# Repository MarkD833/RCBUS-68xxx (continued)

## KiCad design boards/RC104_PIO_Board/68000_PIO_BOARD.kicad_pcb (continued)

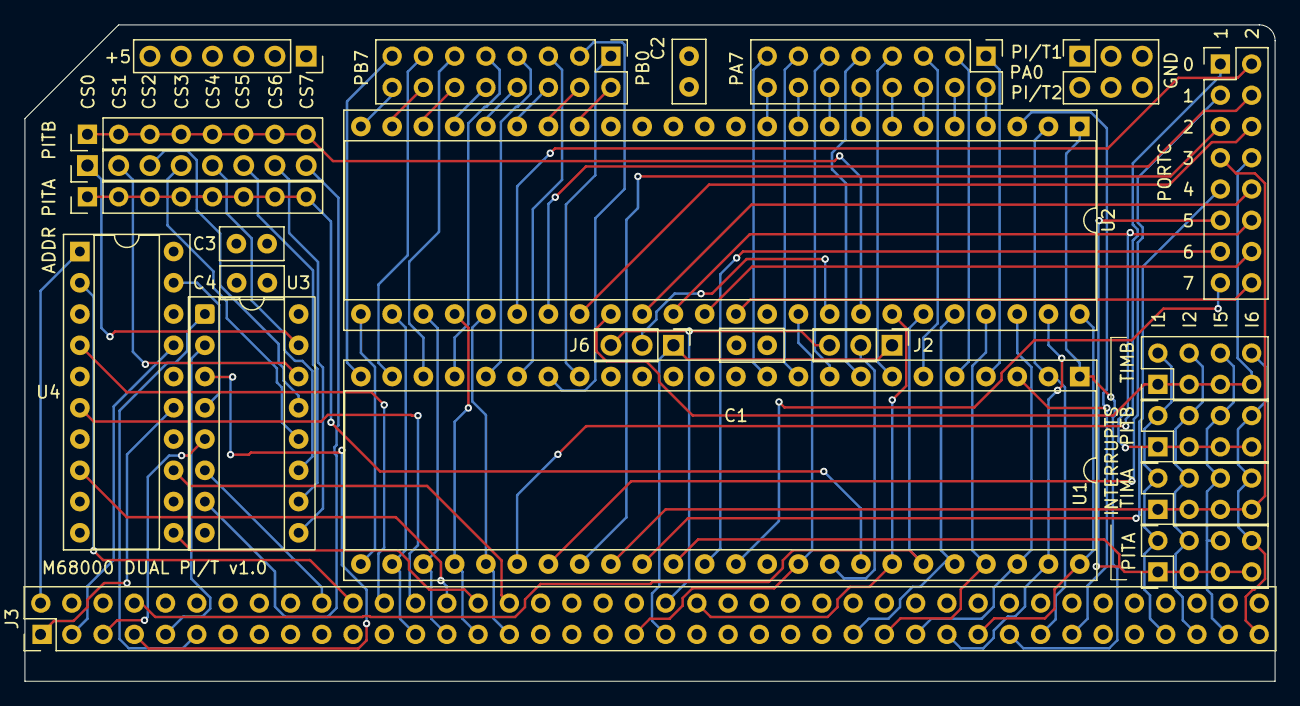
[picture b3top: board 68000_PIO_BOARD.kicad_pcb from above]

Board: 4 copper layers, 101.6 x 53.3 mm, 23 parts (0 on the bottom side), 99 nets.

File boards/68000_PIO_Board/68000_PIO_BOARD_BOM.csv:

"Reference","Value","Datasheet","Footprint","Qty","Description"
"C1,C2,C3,C4","100n","~","Capacitor_THT:C_Disc_D5.0mm_W2.5mm_P2.50mm","4","Unpolarized ceramic capacitor"
"J1,J4,J5","Conn_02x08_Odd_Even","~","MyLibrary2023:PinHeader_2x08_P2.54mm_Vertical","3","Generic connector, double row, 02x08, right angle"
"J2,J6","Conn_01x03","~","Connector_PinHeader_2.54mm:PinHeader_1x03_P2.54mm_Vertical","2","Generic connector, single row, 01x03"
"J3","RCBus_80PIN_68000","~","MyLibrary2023:RCBus_80p_Medium","1","Generic connector, double row, 02x40, right angle"
"J7,J12,J13","Conn_01x08","~","Connector_PinHeader_2.54mm:PinHeader_1x08_P2.54mm_Vertical,MyLibrary2023:PinHeader_1x08_P2.54mm_Vertical","3","Generic connector, single row, 01x08"
"J8,J9,J10,J11","Conn_02x04_Odd_Even","~","MyLibrary2023:PinHeader_2x04_P2.54mm_Vertical","4","Generic connector, double row, 02x04"
"J14","Conn_02x03_Odd_Even","~","Connector_PinSocket_2.54mm:PinSocket_2x03_P2.54mm_Vertical","1","Generic connector, double row, 02x03, right angle"
"J15","Conn_01x06","~","Connector_PinSocket_2.54mm:PinSocket_1x06_P2.54mm_Vertical","1","Generic connector, single row, 01x06, right angle"
"U1,U2","68230","","MyLibrary2023:DIP-48_W15.24mm_Socket","2","Parallel Interface / Timer"
"U3","74LS138","http://www.ti.com/lit/gpn/sn74LS138","Package_DIP:DIP-16_W7.62mm_Socket","1","Decoder 3 to 8 active low outputs"
"U4","74LS688","http://www.ti.com/lit/gpn/sn74LS688","MyLibrary2023:DIP-20_W7.62mm_Socket","1","8-bit magnitude comparator"

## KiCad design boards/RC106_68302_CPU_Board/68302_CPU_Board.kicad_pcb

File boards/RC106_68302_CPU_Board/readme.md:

# 68302 Processor Board

# Details
The processor board consists of a PGA packaged MC68302 processor, bits of glue logic and the processor clock source.

The processor board is designed to plug into an RCBus-80 backplane and expects to find the stack pointer and initial program counter addresses at location 0x000000 onwards.

If using latest version of the MON302 that supports ROM & RAM remapping via software then the RC102 ROM/RAM board should not be used without some hardware modification.

## Reset
The reset signal for the processor board must be supplied externally, entering the board via pin 20 of the RCBus connector. This should not be an issue if you are using one of Steve Cousins's backplanes.

## Processor Clock
The processor/system clock source is an oscillator in an 8-pin DIL/DIP can (X1 in the schematic). I used a turned pin socket to hold the oscillator as it made it easy to quickly swap in and out oscillators of different frequencies. Basic testing was done with a 7.3728MHz oscillator.

A **note of caution** when using a socketed oscillator - there is the possibility that the metal can of the oscillator could accidentally short out pins on the next board. Please be aware of this.

The 68302 doesn't have an E clock signal like the 68000 does so I chose to have the option to route the output of Timer #1 to the RCBus CLOCK2 pin (61) via a jumper.

Note that the CLOCK2 pin may also be used by the serial, parallel and multifunction boards (via jumpers on their boards) to share a clock source between them - usually to feed the baud rate generators and timers. If this feature is used, then the CLOCK2 jumper must not be fitted.

## Chip Selects
The 68302 processor has 4 user programmable chip select signals - /CS0, /CS1, /CS2 & /CS3.

/CS0 is automatically configured by the processor at reset for an 8K block of memory starting at address $000000. /CS0 would normally be used to select a non-volatile memory device that holds the boot code. However there's a solder jumper (JP1) that can be used to route /CS0 to RCBus pin 45 if required.
+ RC102 ROM/RAM board includes address decoding to select the pair of ROMs at address $000000 so /CS0 isn't needed (must use older version of MON302)
+ RC107 ROM/RAM board supports external chip selects - see RC107 readme for more details
+ RC208 ROM/RAM board **MUST** set the ROM chip select to EXT

/CS1 is disabled by the processor at reset. I intended this chip select to select the volatile memory device on my RC107 ROM/RAM board. There's a solder jumper (JP2) that can be used to route /CS1 to RCBus pin 46 if required.
+ RC102 ROM/RAM board includes address decoding to select the pair of RAMs at address $100000 so /CS1 isn't needed (must use older version of MON302)
+ RC107 ROM/RAM board supports external chip selects - see RC107 readme for more details
+ RC208 ROM/RAM board **MUST** set the RAM chip select to EXT

/CS2 is disabled by the processor at reset. This chip select signal is used to enable access to the RCBus memory and i/o spaces. The /CS2 address decoding is configured for a 128K block of memory that is split into two 64K blocks by half of a 74LS139. Accessing the lower 64K block generates an /MREQ on the RCBus and accessing the upper 64K block generates an /IORQ on the RCBus.

**NOTE:** If using the newer version of MON302 that supports remapping of the ROM and RAM address spaces, then please see the relevant ROM/RAM board readme file for details on the hardware modifications needed to the ROM/RAM board to support this.

## DTACK & Bus Error
The user programmable chip select signals can also be configured to internally generate the DTACK signal so no external gates are required. My ROM/RAM board generates its own DTACK signal so DTACK is disabled for /CS0 & /CS1. /CS2 is configured to for 2 wait states.

The 68302 processor also includes an internal hardware watchdog that is enabled at reset and will generate a Bus Error if a DTACK isn't generated by the internal chip select logic or an external device.

## Serial Ports
Two of the 68302 serial ports - SCC1 & SCC2 - are fed to 6-pin connectors at the board edge. The layout of the 6 pins is compatible with an FTDI USB-TTL Serial interface board.

## SPI Port
The 68302 hardware SPI port (via SCC3 pins) is available on J6. Also on J6 is a chip select for the SPI device which is connected to port pin PB8 of the 68302.
 
## RCBus Signals
The RCBus specification (v1.0) doesn't specifically mention the 68000 in the backplane signal assignments table so there's a bit of wiggle room on the pins used.

I've stuck to the same signals for pins 1-40. The M1 signal isn't used and should have a 4K7 pullup resistor (manually added as I forgot it in my release 2.0 board!) and the USER1..USER4 which are used for the level 1, 3, 5 & 6 autovector interrupts.

Pins 41-80 carry D8..D15 as well as the higher address bits. Pins 41..44 have been used to carry some 68000 specific signals.

The current signal list is in the RCBus 68000 Pinout PDF file.

For the 68302 board, I have introduced 2 additional signals that can be routed onto the backplane to expose the /CS0 (pin 45) and /CS1 (pin 46) chip select signals. These are disconnected by default but can easily be connected by shorting solder jumpers JP1 (/CS0) and JP2 (/CS1) on the rear of the board.

The output of Timer #1 can be routed to the CLOCK2 pin to provide a clock source for other boards if required.

## RCBus memory space
The RCBus memory space is available via a 128K window in the 68302 address space. The hardware uses /CS2 to select this memory space with A16 determining either memory or I/O space as follows:
| Address Range | Signal |
| :---- | :---- |
| 0xFC0000..0xFCFFFF | /MREQ goes low |
| 0xFD0000..0xFDFFFF | /IORQ goes low |

This partial decoding results in the RCBus I/O memory space appearing multiple times within the 68000 address range. A DTACK signal is generated internally for any access to the RCBus whether there is a device present at that address or not.

For both I/O and memory spaces, consecutive memory locations are accessed on the ODD bytes such that I/O address 0x00 is accessed at address 0xFD0001, address 0x01 is accessed at address 0xFD0003 etc.

## Onboard LEDs
There are 4 LEDs on the board indicate accesses to the RCBus I/O and memory spaces as well as a HALT LED and a user LED (connected to port pin PB9).

## Power
The complete RCBus system can be powered from the 5V pin of one of the USB-TTL serial connectors by fitting a jumper in place on the appropriate pins of J3.

Note that there is a current limit of 500mA - imposed by the host system USB hardware - when the system is powered this way. It is relatively easy to exceed this limit once several boards are in use and I recommend that the system be powered from an external 5V supply connected to the RCBus backplane instead.

# Board Assembly
Assembly of the board should be fairly straightforward as there are no surface mount devices to deal with, but see the note below regarding the 68302 socket.

If you choose have a turned pin socket for the system clock, then an 8-pin DIL turned pin socket can be used. I flipped the socket over - pins pointing upwards - and easily pushed out pins 2,3,6 & 7.

A **note of caution** when using a socketed oscillator - there is the possibility that the metal can of the oscillator could accidentally short out pins on the next board. Please be aware of this.

When fitting the 80-pin right angle connector, initially only solder a couple of pins at opposite ends of the connector so that you can make any adjustments if the board is not vertical when fitted to the backplane.

# Note on the MC68302 socket
I could not get hold of the official PGA socket for the 68302 so I had to make my own from some SIL turned pin socket strips. From an earlier experiment I learnt that the plastic housing is slightly too wide so you can't simply butt together 13 SIL strips to make a socket. Instead I had to alternate between rows of pins in the plastic housing and rows of individual pins like this:

This makes it a bit of a pain trying to get all the individual pins to play ball and line up with the PCB holes but it does work.

**Note:** Be careful with this method as I later discovered that the SIL turned pin sockets were not the low insertion force type. Once soldered into the board, the combined resistance of 132 turned pin sockets is such that the processor can't be removed without breaking it. The only way to get the processor out safely is by destroying the board with a handy rotary tool by cutting out the piece of board holding the processor and then carefully cutting off the pins very close to the board. The processor should then come away and the remains of the turned pin sockets can be easily removed individually. 

# Software
I've written a very simple monitor program for the 68302 board whick can be found in the ASM_CODE folder - called MON302. The monitor was initially developed using EASy68K.

## Interrupts
As the ROM is currently fixed at address 0x000000, the exception vector table addresses are also fixed. Exception vectors up to and including TRAP #15 each call their own handler stub within the monitor ROM. The remaining exception vectors are all directed to a single handler as they are not used within my design - i.e. vectored interrupts are not supported, only autovectored interrupts.

Each exception handler stub in the ROM (apart from bus error, address error and TRAP #15) looks up the start address of the actual exception handler code in a table of addresses held in RAM (which is initialised by the montor program). The table is located at the start of RAM occupying addresses 0x100000..0x1003FF and is laid out just like a normal exception vector table.

In order to use your own exception handler, you simply over write the RAM exception vector table entry with the address of your own handler.

# Jumpers
+ J1: Fit jumper to route Timer #1 output onto RCBus CLOCK2 but only if CLOCK2 is **not** being used to share a clock between the SIO, PIO and MFP boards.
+ J3: External 5V supply for the system
  + 1-2 : Power the system from the USB-TTL Serial board on Serial #1
  + 2-3 : Power the system from the USB-TTL Serial board on Serial #2
+ J4: Serial #1 port from SCC1
+ J5: Serial #2 port from SCC2
+ J6: SPI port

# Solder Jumpers
The 2 solder jumpers are located on the rear of the board and are used to route the 68302 /CS0 and /CS1 chip select signals onto the RCBus. With these jumpers soldered and a simple modification to the ROM/RAM board, the 68302 can boot from ROM at address $0000 and then swap the ROM and RAM so that RAM is located at address $0000.

+ JP1: solder this jumper to connect /CS0 to RCBus pin 45.
+ JP2: solder this jumper to connect /CS1 to RCBus pin 46.

# Errors
A fundamental flaw in the way interrupts are handled has come to light. This appears to only affect interrupts generated internally by the 68302 such as serial port or timer interrupts. It seems that when the 68302 generates its own interrupt - when an SCC receive buffer is full for example - it exposes this interrupt to the outside world by setting its FC0, FC1 & FC2 bits to a 7. This causes the current external logic to drive the /AVEC pin and create a level 4 autovectored interrupt rather than a level 4 vectored interrupt. All 68302 internally generated interrupts are level 4. The end result is that all internally generated interrupts get funneled through the single AV4 exception handler.

# Thoughts / Enhancements
+ Should I have used SCC1 for the monitor port?
  + CTS1 is in input to SCC1 that can be used to tell SCC1 to stop transmitting.
  + RTS1 is an output from SCC1 and is asserted when SCC1 Tx buffer has data to send.
  + Don't appear to have software control over these pins to be able to tell the host PC to stop transmitting data to SCC1.
+ SCC2 provides software control of RTS2 (Port pin PA5) and CTS2 (Port pin PA4). Therefore can tell host PC to stop transmitting via software if our Rx buffers fill up.
+ SCC3 has no handshaking as the pins are used for the SPI interface.
+ For 115200 baud with RTS/CTS handshaking for quick xfer of srec files then it looks like SCC2 would be the better choice.

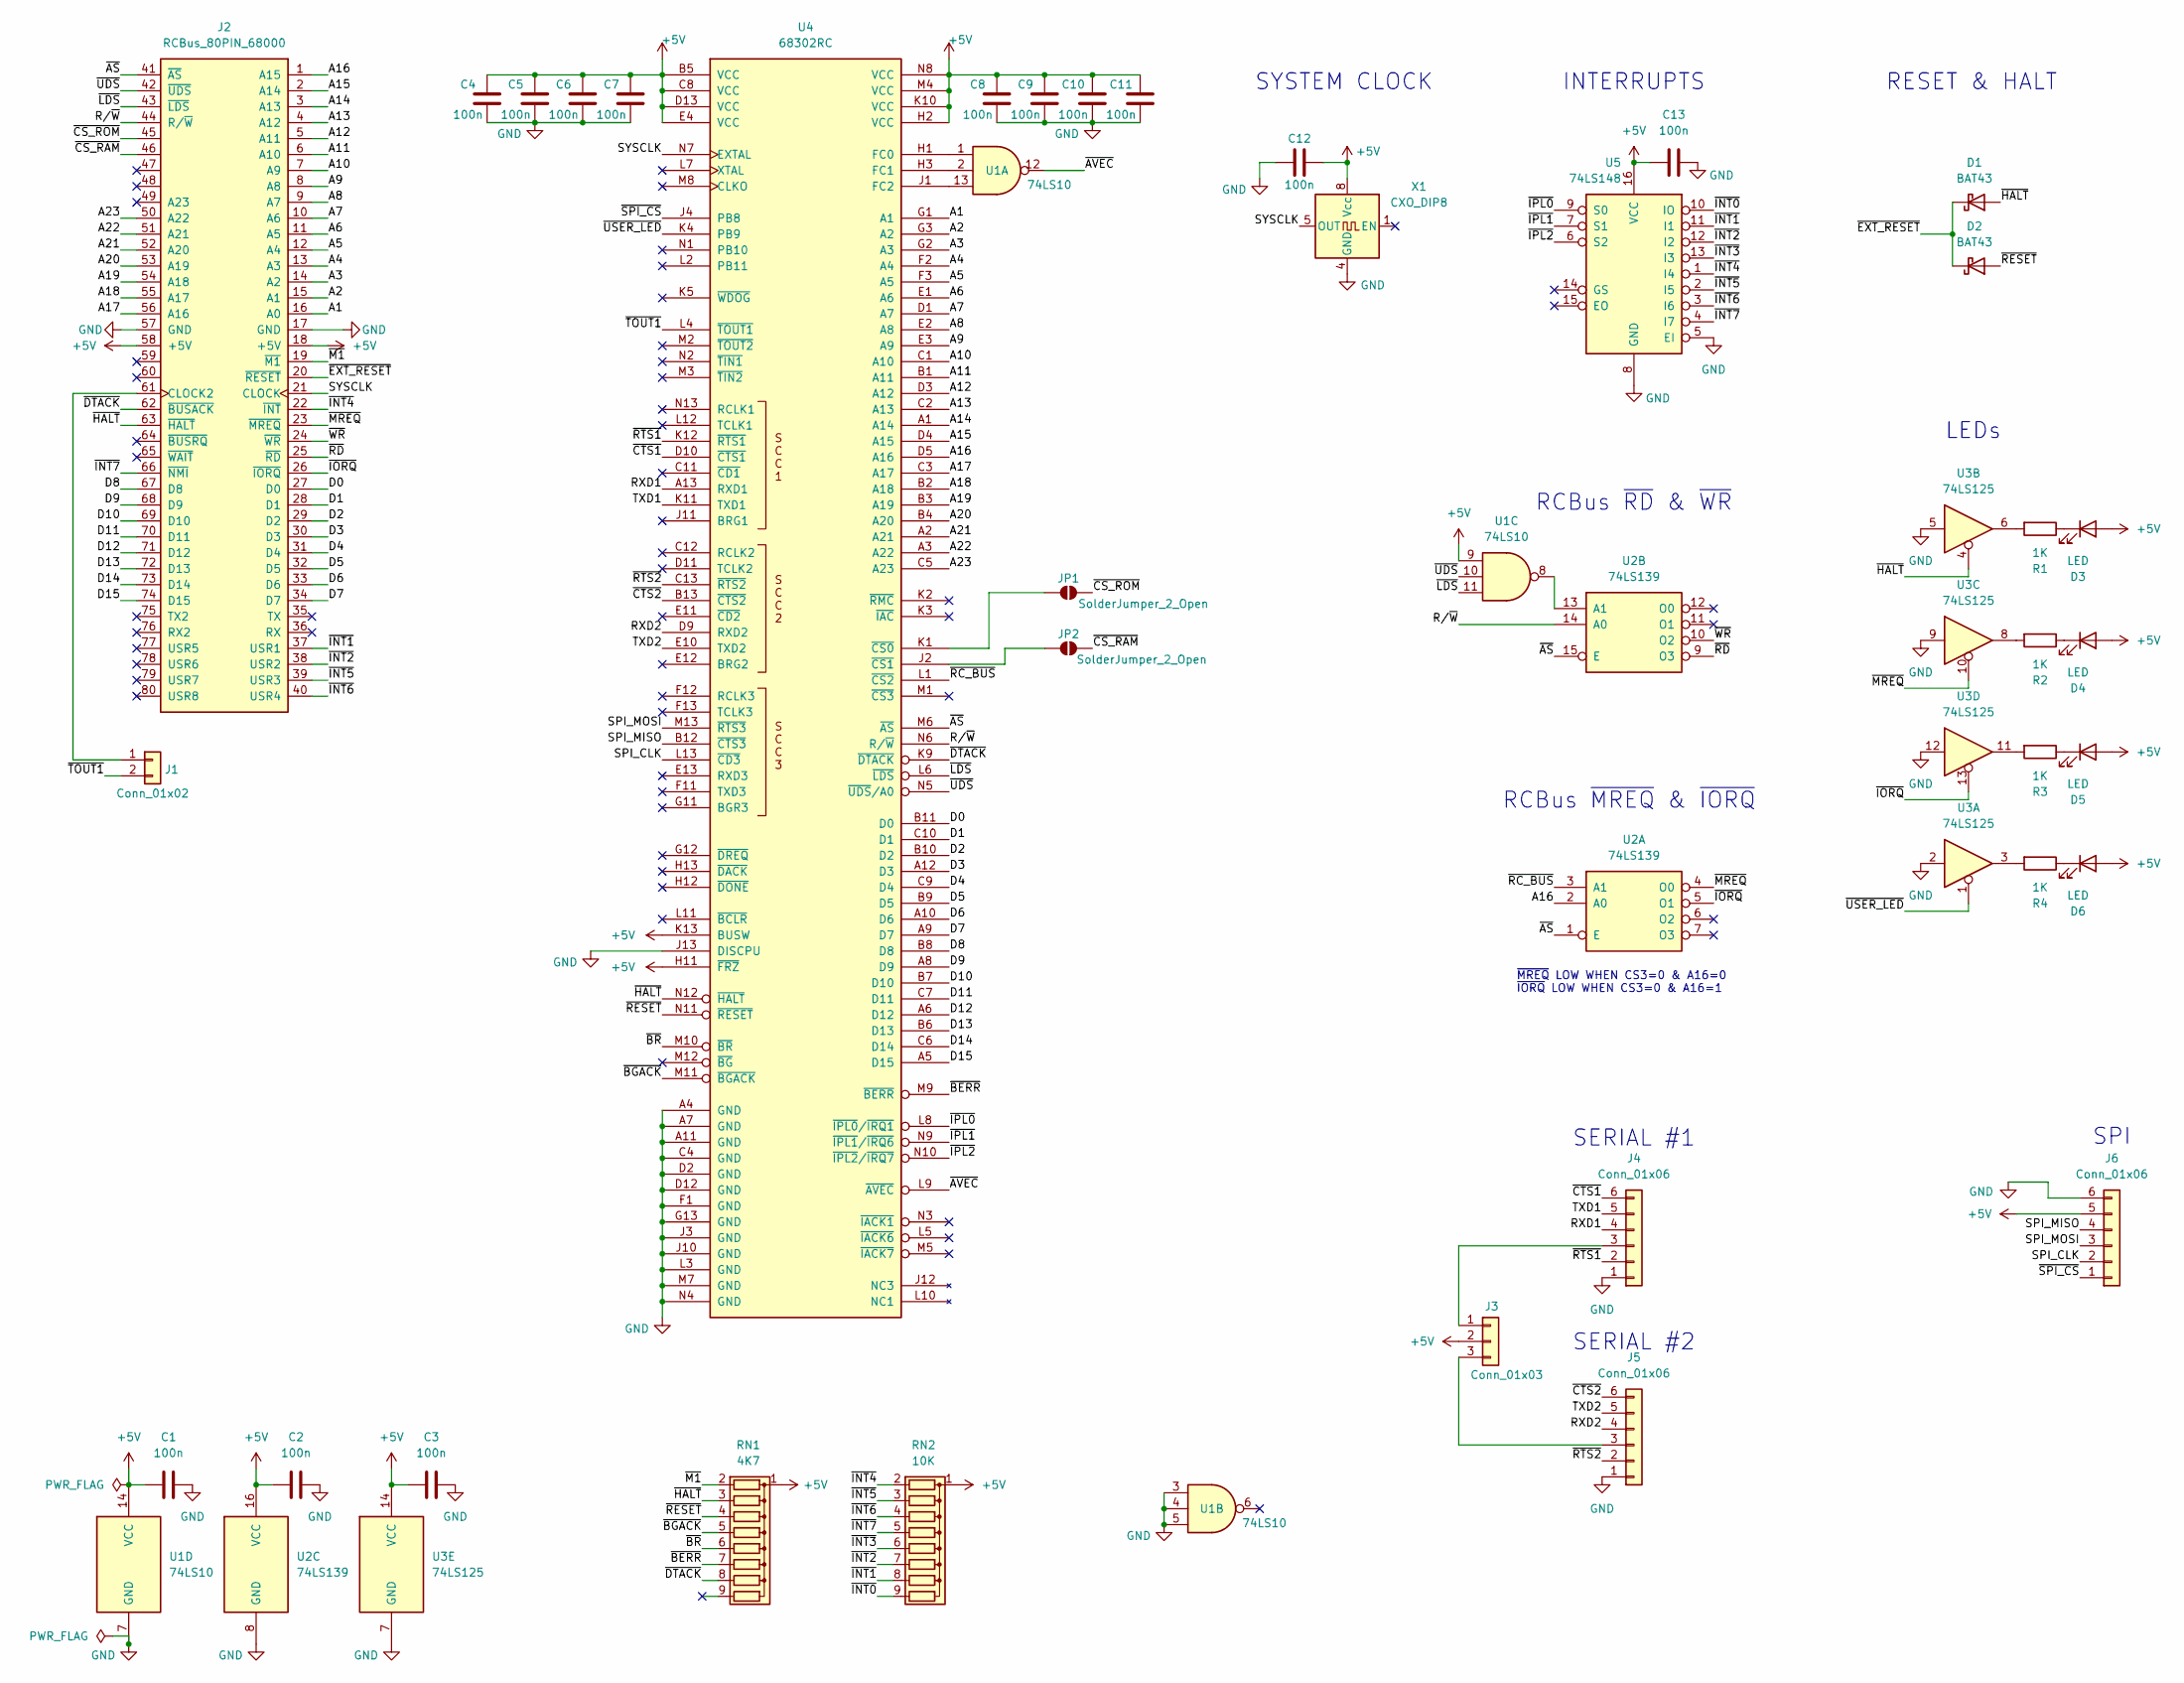
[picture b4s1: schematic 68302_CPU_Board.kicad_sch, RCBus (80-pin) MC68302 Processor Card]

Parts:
C1, C2, C3, C4, C5, C6, C7, C8, C9, C10, C11, C12, C13: 100n; C_Disc_D5.0mm_W2.5mm_P2.50mm
D1, D2: BAT43; D_DO-35_SOD27_P7.62mm_Horizontal
D3, D4, D5, D6: LED; LED_D3.0mm
J1: Conn_01x02; PinHeader_1x02_P2.54mm_Vertical
J2: RCBus_80PIN_68000; RCBus_80p_Medium
J3: Conn_01x03; PinHeader_1x03_P2.54mm_Vertical
J4, J5, J6: Conn_01x06; PinSocket_1x06_P2.54mm_Horizontal
JP1, JP2: SolderJumper_2_Open; SolderJumper-2_P1.3mm_Open_Pad1.0x1.5mm
R1, R2, R3, R4: 1K; R_Axial_DIN0207_L6.3mm_D2.5mm_P7.62mm_Horizontal
RN1: 4K7; R_Array_SIP9
RN2: 10K; R_Array_SIP9
U1: 74LS10; DIP-14_W7.62mm_Socket
U2: 74LS139; DIP-16_W7.62mm_Socket
U3: 74LS125; DIP-14_W7.62mm_Socket
U4: 68302RC; PGA132
U5: 74LS148; DIP-16_W7.62mm_Socket
X1: CXO_DIP8; Oscillator_DIP-8

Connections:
+5V: C1.1, C2.1, C3.1, C4.2, C5.2, C6.2, C7.2, C8.2, C9.2, C10.2, C11.2, C12.2, C13.1, D3.2 (A), D4.2 (A), D5.2 (A), D6.2 (A), J2.18 (+5V), J2.58 (+5V), J3.2, J6.5, RN1.1 (common), RN2.1 (common), U1.9, U1.14 (VCC), U2.16 (VCC), U3.14 (VCC), U4.B5 (VCC), U4.C8 (VCC), U4.D13 (VCC), U4.E4 (VCC), U4.H2 (VCC), U4.H11 (~FRZ), U4.K10 (VCC), U4.K13 (BUSW), U4.M4 (VCC), U4.N8 (VCC), U5.16 (VCC), X1.8 (Vcc)
/A1: J2.16 (A0), U4.G1 (A1)
/A2: J2.15 (A1), U4.G3 (A2)
/A3: J2.14 (A2), U4.G2 (A3)
/A4: J2.13 (A3), U4.F2 (A4)
/A5: J2.12 (A4), U4.F3 (A5)
/A6: J2.11 (A5), U4.E1 (A6)
/A7: J2.10 (A6), U4.D1 (A7)
/A8: J2.9 (A7), U4.E2 (A8)
/A9: J2.8 (A8), U4.E3 (A9)
/A10: J2.7 (A9), U4.C1 (A10)
/A11: J2.6 (A10), U4.B1 (A11)
/A12: J2.5 (A11), U4.D3 (A12)
/A13: J2.4 (A12), U4.C2 (A13)
/A14: J2.3 (A13), U4.A1 (A14)
/A15: J2.2 (A14), U4.D4 (A15)
/A16: J2.1 (A15), U2.2 (A0), U4.D5 (A16)
/A17: J2.56 (A16), U4.C3 (A17)
/A18: J2.55 (A17), U4.B2 (A18)
/A19: J2.54 (A18), U4.B3 (A19)
/A20: J2.53 (A19), U4.B4 (A20)
/A21: J2.52 (A20), U4.A2 (A21)
/A22: J2.51 (A21), U4.A3 (A22)
/A23: J2.50 (A22), U4.C5 (A23)
/D0: J2.27 (D0), U4.B11 (D0)
/D1: J2.28 (D1), U4.C10 (D1)
/D2: J2.29 (D2), U4.B10 (D2)
/D3: J2.30 (D3), U4.A12 (D3)
/D4: J2.31 (D4), U4.C9 (D4)
/D5: J2.32 (D5), U4.B9 (D5)
/D6: J2.33 (D6), U4.A10 (D6)
/D7: J2.34 (D7), U4.A9 (D7)
/D8: J2.67 (D8), U4.B8 (D8)
/D9: J2.68 (D9), U4.A8 (D9)
/D10: J2.69 (D10), U4.B7 (D10)
/D11: J2.70 (D11), U4.C7 (D11)
/D12: J2.71 (D12), U4.A6 (D12)
/D13: J2.72 (D13), U4.B6 (D13)
/D14: J2.73 (D14), U4.C6 (D14)
/D15: J2.74 (D15), U4.A5 (D15)
/RXD1: J4.4, U4.A13 (RXD1)
/RXD2: J5.4, U4.D9 (RXD2)
/R/~W: J2.44 (R/~W), U2.14 (A0), U4.N6 (R/~W)
/SPI_CLK: J6.2, U4.L13 (~CD3)
/SPI_MISO: J6.4, U4.B12 (~CTS3)
/SPI_MOSI: J6.3, U4.M13 (~RTS3)
/SYSCLK: J2.21 (CLOCK), U4.N7 (EXTAL), X1.5 (OUT)
/TXD1: J4.5, U4.K11 (TXD1)
/TXD2: J5.5, U4.E10 (TXD2)
/~AS: J2.41 (~AS), U2.1 (E), U2.15 (E), U4.M6 (~AS)
/~AVEC: U1.12, U4.L9 (~AVEC)
/~BERR: RN1.7 (R6), U4.M9 (~BERR)
/~BGACK: RN1.5 (R4), U4.M11 (~BGACK)
/~BR: RN1.6 (R5), U4.M10 (~BR)
/~CS_RAM: J2.46, JP2.2 (B)
/~CS_ROM: J2.45, JP1.2 (B)
/~CTS1: J4.6, U4.D10 (~CTS1)
/~CTS2: J5.6, U4.B13 (~CTS2)
/~DTACK: J2.62 (~BUSACK), RN1.8 (R7), U4.K9 (~DTACK)
/~EXT_RESET: D1.1 (K), D2.1 (K), J2.20 (~RESET)
/~HALT: D1.2 (A), J2.63 (~HALT), RN1.3 (R2), U3.4, U4.N12 (~HALT)
/~INT0: RN2.9 (R8), U5.10 (IO)
/~INT1: J2.37 (USR1), RN2.8 (R7), U5.11 (I1)
/~INT2: J2.38 (USR2), RN2.7 (R6), U5.12 (I2)
/~INT3: RN2.6 (R5), U5.13 (I3)
/~INT4: J2.22 (~INT), RN2.2 (R1), U5.1 (I4)
/~INT5: J2.39 (USR3), RN2.3 (R2), U5.2 (I5)
/~INT6: J2.40 (USR4), RN2.4 (R3), U5.3 (I6)
/~INT7: J2.66 (~NMI), RN2.5 (R4), U5.4 (I7)
/~IORQ: J2.26 (~IORQ), U2.5 (O1), U3.13
/~IPL0: U4.L8 (~IPL0/~IRQ1), U5.9 (S0)
/~IPL1: U4.N9 (~IPL1/~IRQ6), U5.7 (S1)
/~IPL2: U4.N10 (~IPL2/~IRQ7), U5.6 (S2)
/~LDS: J2.43 (~LDS), U1.11, U4.L6 (~LDS)
/~M1: J2.19 (~M1), RN1.2 (R1)
/~MREQ: J2.23 (~MREQ), U2.4 (O0), U3.10
/~RC_BUS: U2.3 (A1), U4.L1 (~CS2)
/~RD: J2.25 (~RD), U2.9 (O3)
/~RESET: D2.2 (A), RN1.4 (R3), U4.N11 (~RESET)
/~RTS1: J4.2, U4.K12 (~RTS1)
/~RTS2: J5.2, U4.C13 (~RTS2)
/~SPI_CS: J6.1, U4.J4 (PB8)
/~TOUT1: J1.2, U4.L4 (~TOUT1)
/~UDS: J2.42 (~UDS), U1.10, U4.N5 (~UDS/A0)
/~USER_LED: U3.1, U4.K4 (PB9)
/~WR: J2.24 (~WR), U2.10 (O2)
GND: C1.2, C2.2, C3.2, C4.1, C5.1, C6.1, C7.1, C8.1, C9.1, C10.1, C11.1, C12.1, C13.2, J2.17 (GND), J2.57 (GND), J4.1, J5.1, J6.6, U1.3, U1.4, U1.5, U1.7 (GND), U2.8 (GND), U3.2, U3.5, U3.7 (GND), U3.9, U3.12, U4.A4 (GND), U4.A7 (GND), U4.A11 (GND), U4.C4 (GND), U4.D2 (GND), U4.D12 (GND), U4.F1 (GND), U4.G13 (GND), U4.J3 (GND), U4.J10 (GND), U4.J13 (DISCPU), U4.L3 (GND), U4.M7 (GND), U4.N4 (GND), U5.5 (EI), U5.8 (GND), X1.4 (GND)
unnamed: D3.1 (K), R1.1
unnamed: D4.1 (K), R2.1
unnamed: D5.1 (K), R3.1
unnamed: D6.1 (K), R4.1
unnamed: J1.1, J2.61 (CLOCK2)
unnamed: J3.1, J4.3
unnamed: J3.3, J5.3
unnamed: JP1.1 (A), U4.K1 (~CS0)
unnamed: JP2.1 (A), U4.J2 (~CS1)
unnamed: R1.2, U3.6
unnamed: R2.2, U3.8
unnamed: R3.2, U3.11
unnamed: R4.2, U3.3
unnamed: U1.8, U2.13 (A1)
unnamed: U1.1, U4.H1 (FC0)
unnamed: U1.2, U4.H3 (FC1)
unnamed: U1.13, U4.J1 (FC2)

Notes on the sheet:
SYSTEM CLOCK
SERIAL #2
SPI
SERIAL #1
LEDs
INTERRUPTS
RCBus ~{MREQ} & ~{IORQ}
~{MREQ} LOW WHEN CS3=0 & A16=0 ~{IORQ} LOW WHEN CS3=0 & A16=1
RCBus ~{RD} & ~{WR}
RESET & HALT

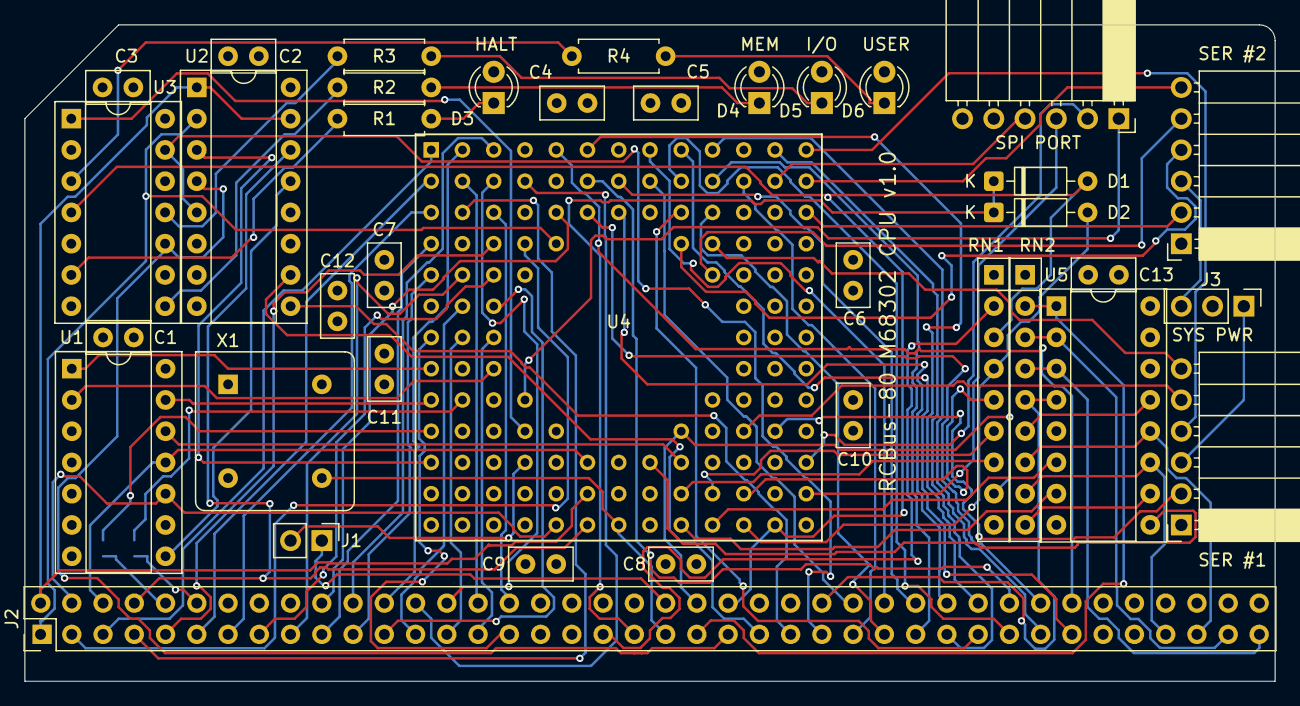
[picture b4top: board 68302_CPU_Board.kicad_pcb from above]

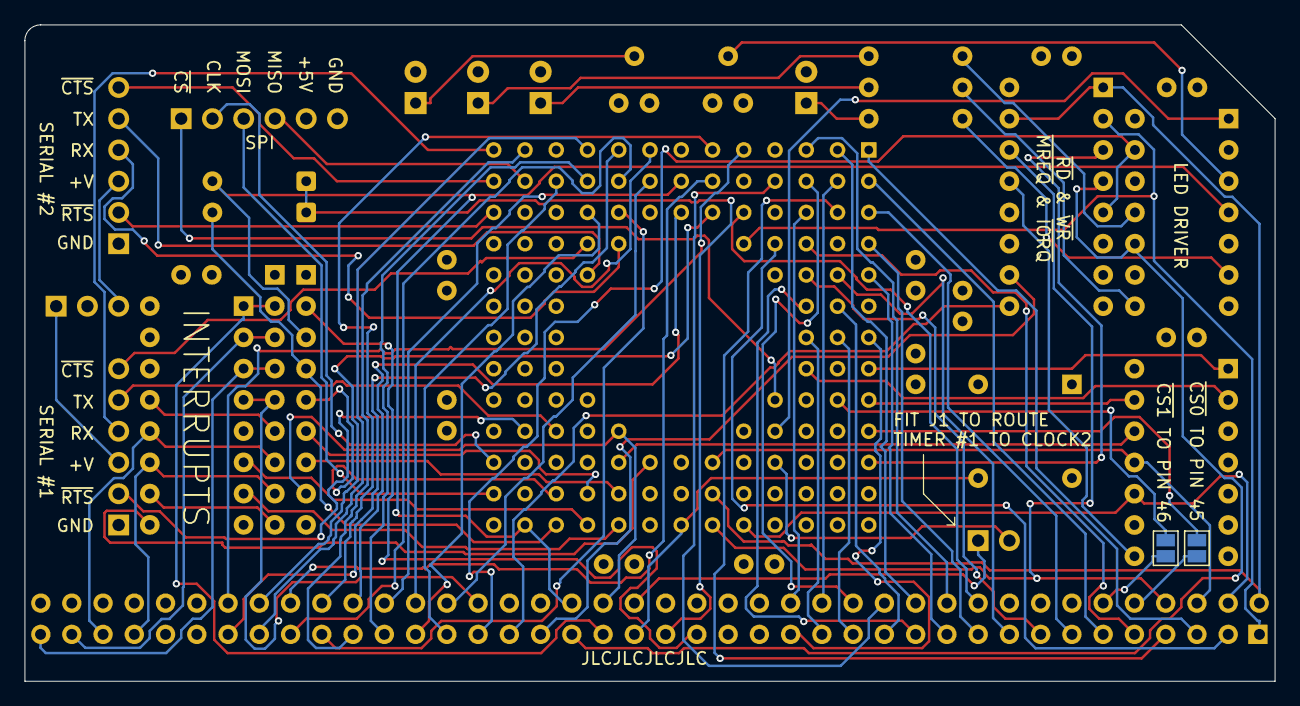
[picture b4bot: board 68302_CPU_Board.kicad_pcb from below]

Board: 4 copper layers, 101.6 x 53.3 mm, 39 parts (2 on the bottom side), 104 nets.

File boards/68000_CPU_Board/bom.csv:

Designator,Footprint,Quantity,Value,LCSC Part #
"C1, C10, C11, C2, C3, C5, C6, C7, C8, C9",C_Disc_D5.0mm_W2.5mm_P2.50mm,10,100n,
"D1, D2",D_DO-35_SOD27_P7.62mm_Horizontal,2,BAT43,
"D3, D4, D5",LED_D3.0mm,3,LED,
J1,PinHeader_2x04_P2.54mm_Vertical,1,Conn_02x04_Odd_Even,
J2,RCBus_80p_Medium,1,RCBus_80PIN_68000,
J4,PinHeader_1x02_P2.54mm_Vertical,1,Conn_01x02,
"R1, R2, R3",R_Axial_DIN0207_L6.3mm_D2.5mm_P7.62mm_Horizontal,3,1K,
RN1,R_Array_SIP9,1,4K7,
RN2,R_Array_SIP9,1,10K,
U1,PLCC-68_THT-Socket,1,MC68000FN,
U2,DIP-14_W7.62mm_Socket,1,74LS125,
U3,DIP-16_W7.62mm_Socket,1,74LS148,
U4,DIP-14_W7.62mm_Socket,1,74LS10,
U5,DIP-16_W7.62mm_Socket,1,74LS139,
"U6, U8",DIP-16_W7.62mm_Socket,2,74LS175,
U9,DIP-14_W7.62mm_Socket,1,74LS00,
X1,Oscillator_DIP-8,1,CXO_DIP8,

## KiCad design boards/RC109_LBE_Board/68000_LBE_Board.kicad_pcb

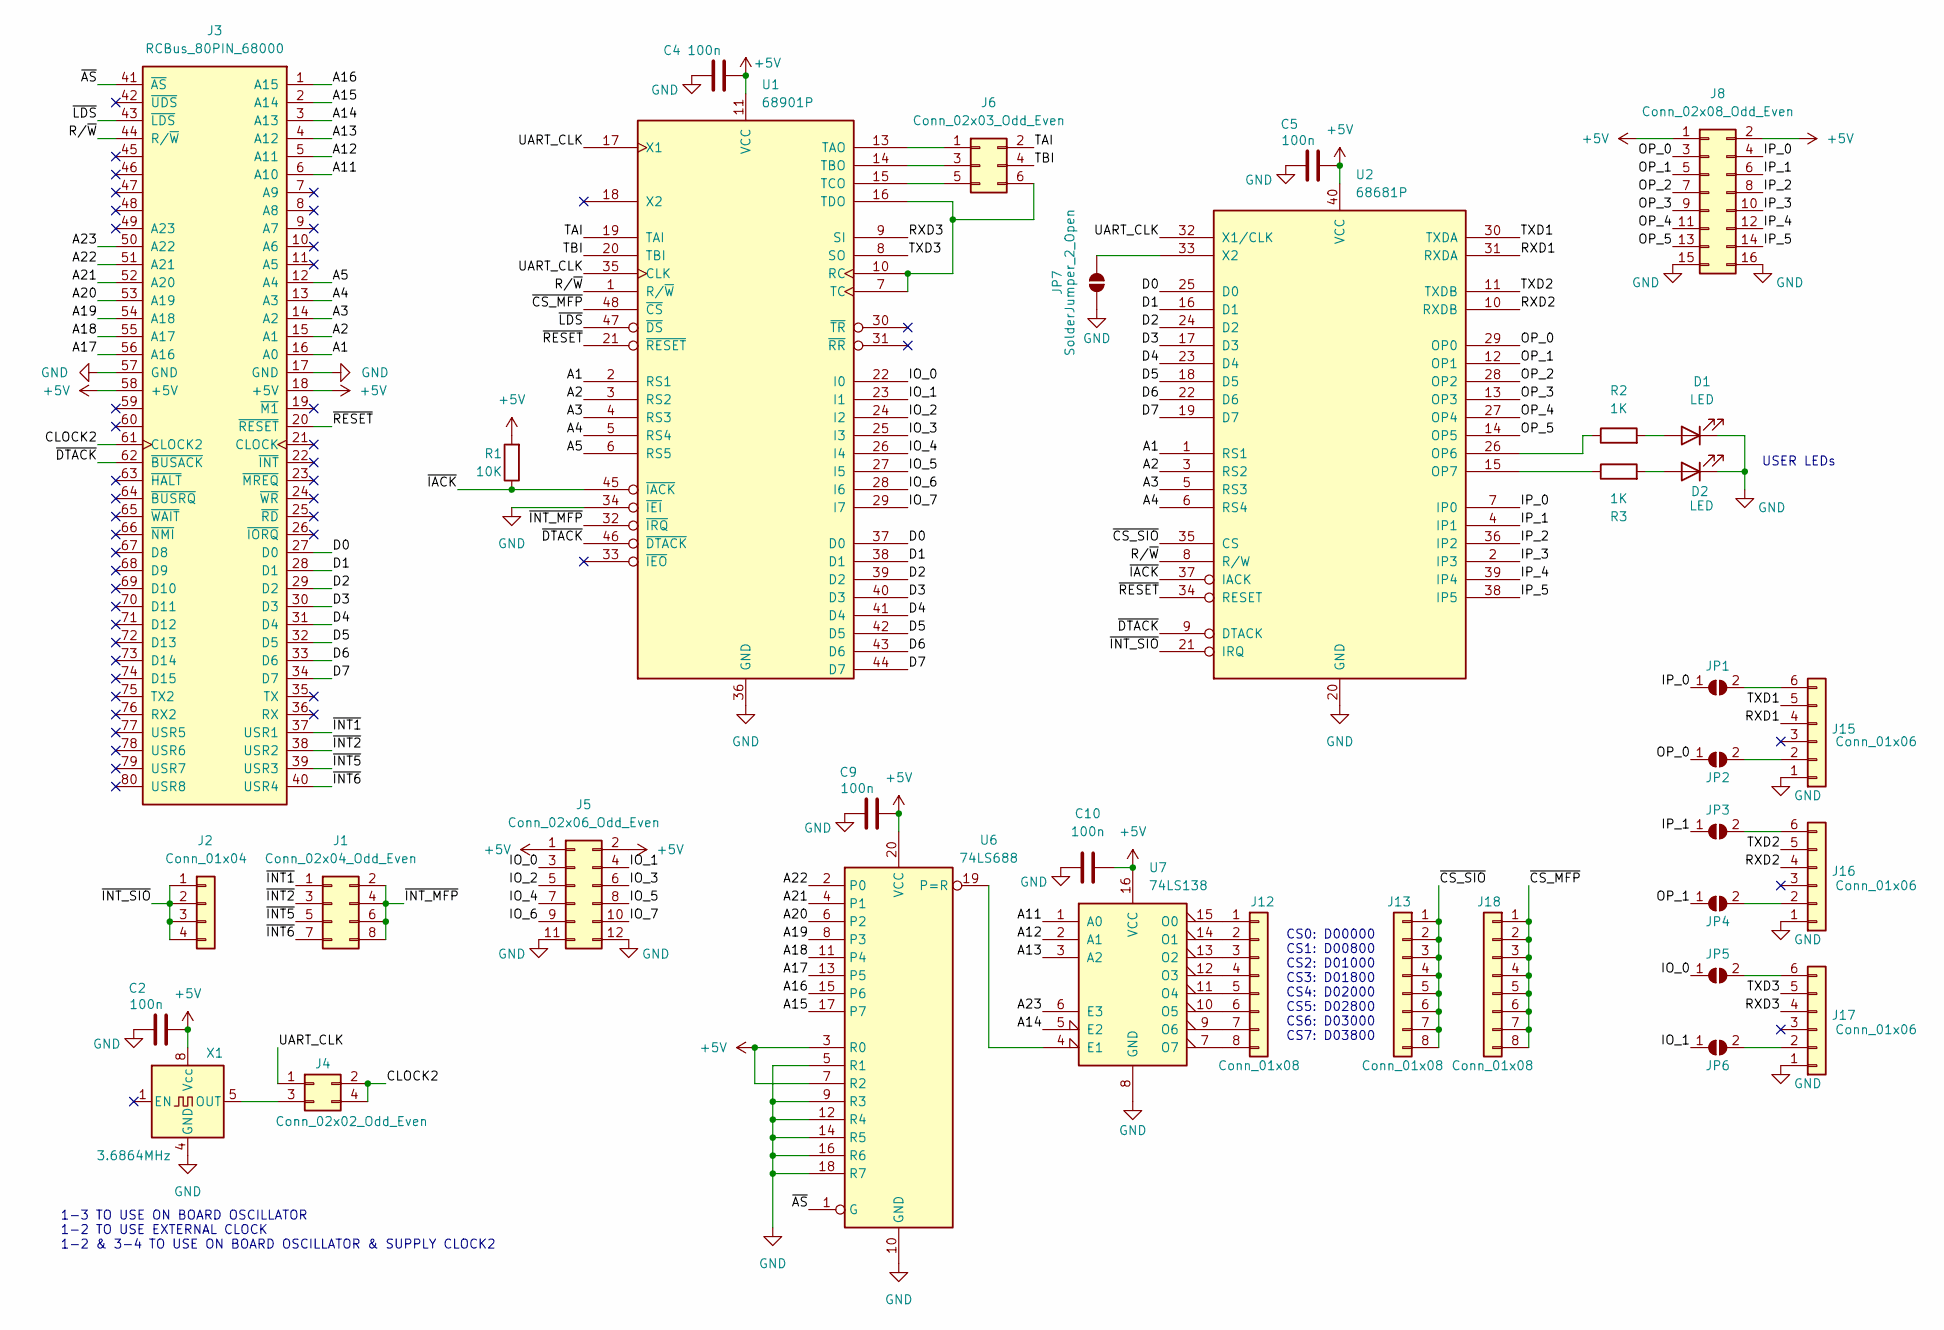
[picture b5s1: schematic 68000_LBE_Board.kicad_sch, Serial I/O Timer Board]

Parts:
C2, C4, C5, C9, C10: 100n; C_Disc_D5.0mm_W2.5mm_P2.50mm
D1, D2: LED; LED_D3.0mm
J1: Conn_02x04_Odd_Even; PinHeader_2x04_P2.54mm_Vertical
J2: Conn_01x04; PinHeader_1x04_P2.54mm_Vertical
J3: RCBus_80PIN_68000; RCBus_80p_Medium
J4: Conn_02x02_Odd_Even; PinHeader_2x02_P2.54mm_Vertical
J5: Conn_02x06_Odd_Even; PinHeader_2x06_P2.54mm_Horizontal
J6: Conn_02x03_Odd_Even; PinHeader_2x03_P2.54mm_Horizontal
J8: Conn_02x08_Odd_Even; PinHeader_2x08_P2.54mm_Horizontal
J12, J13, J18: Conn_01x08; PinHeader_1x08_P2.54mm_Vertical
J15, J16, J17: Conn_01x06; PinSocket_1x06_P2.54mm_Horizontal
JP1, JP2, JP3, JP4, JP5, JP6: SolderJumper; SolderJumper-2_P1.3mm_Open_Pad1.0x1.5mm
JP7: SolderJumper_2_Open; SolderJumper-2_P1.3mm_Open_Pad1.0x1.5mm
R1: 10K; R_Axial_DIN0207_L6.3mm_D2.5mm_P7.62mm_Horizontal
R2, R3: 1K; R_Axial_DIN0207_L6.3mm_D2.5mm_P7.62mm_Horizontal
U1: 68901P; DIP-48_W15.24mm
U2: 68681P; DIP-40_W15.24mm_Socket
U6: 74LS688; DIP-20_W7.62mm_Socket
U7: 74LS138; DIP-16_W7.62mm_Socket
X1: 3.6864MHz; Oscillator_DIP-8

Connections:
+5V: C2.2, C4.2, C5.2, C9.2, C10.2, J3.18 (+5V), J3.58 (+5V), J5.1, J5.2, J8.1, J8.2, R1.2, U1.11 (VCC), U2.40 (VCC), U6.3 (R0), U6.7 (R2), U6.20 (VCC), U7.16 (VCC), X1.8 (Vcc)
/A1: J3.16 (A0), U1.2 (RS1), U2.1 (RS1)
/A2: J3.15 (A1), U1.3 (RS2), U2.3 (RS2)
/A3: J3.14 (A2), U1.4 (RS3), U2.5 (RS3)
/A4: J3.13 (A3), U1.5 (RS4), U2.6 (RS4)
/A5: J3.12 (A4), U1.6 (RS5)
/A11: J3.6 (A10), U7.1 (A0)
/A12: J3.5 (A11), U7.2 (A1)
/A13: J3.4 (A12), U7.3 (A2)
/A14: J3.3 (A13), U7.5 (E2)
/A15: J3.2 (A14), U6.17 (P7)
/A16: J3.1 (A15), U6.15 (P6)
/A17: J3.56 (A16), U6.13 (P5)
/A18: J3.55 (A17), U6.11 (P4)
/A19: J3.54 (A18), U6.8 (P3)
/A20: J3.53 (A19), U6.6 (P2)
/A21: J3.52 (A20), U6.4 (P1)
/A22: J3.51 (A21), U6.2 (P0)
/A23: J3.50 (A22), U7.6 (E3)
/CLOCK2: J3.61 (CLOCK2), J4.2, J4.4
/D0: J3.27 (D0), U1.37 (D0), U2.25 (D0)
/D1: J3.28 (D1), U1.38 (D1), U2.16 (D1)
/D2: J3.29 (D2), U1.39 (D2), U2.24 (D2)
/D3: J3.30 (D3), U1.40 (D3), U2.17 (D3)
/D4: J3.31 (D4), U1.41 (D4), U2.23 (D4)
/D5: J3.32 (D5), U1.42 (D5), U2.18 (D5)
/D6: J3.33 (D6), U1.43 (D6), U2.22 (D6)
/D7: J3.34 (D7), U1.44 (D7), U2.19 (D7)
/IO_0: J5.3, JP5.1 (A), U1.22 (I0)
/IO_1: J5.4, JP6.1 (A), U1.23 (I1)
/IO_2: J5.5, U1.24 (I2)
/IO_3: J5.6, U1.25 (I3)
/IO_4: J5.7, U1.26 (I4)
/IO_5: J5.8, U1.27 (I5)
/IO_6: J5.9, U1.28 (I6)
/IO_7: J5.10, U1.29 (I7)
/IP_0: J8.4, JP1.1 (A), U2.7 (IP0)
/IP_1: J8.6, JP3.1 (A), U2.4 (IP1)
/IP_2: J8.8, U2.36 (IP2)
/IP_3: J8.10, U2.2 (IP3)
/IP_4: J8.12, U2.39 (IP4)
/IP_5: J8.14, U2.38 (IP5)
/OP_0: J8.3, JP2.1 (A), U2.29 (OP0)
/OP_1: J8.5, JP4.1 (A), U2.12 (OP1)
/OP_2: J8.7, U2.28 (OP2)
/OP_3: J8.9, U2.13 (OP3)
/OP_4: J8.11, U2.27 (OP4)
/OP_5: J8.13, U2.14 (OP5)
/RXD1: J15.4, U2.31 (RXDA)
/RXD2: J16.4, U2.10 (RXDB)
/RXD3: J17.4, U1.9 (SI)
/R/~W: J3.44 (R/~W), U1.1 (R/~W), U2.8 (R/W)
/TAI: J6.2, U1.19 (TAI)
/TBI: J6.4, U1.20 (TBI)
/TXD1: J15.5, U2.30 (TXDA)
/TXD2: J16.5, U2.11 (TXDB)
/TXD3: J17.5, U1.8 (SO)
/UART_CLK: J4.1, U1.17 (X1), U1.35 (CLK), U2.32 (X1/CLK)
/~AS: J3.41 (~AS), U6.1 (G)
/~CS_MFP: J18.1, J18.2, J18.3, J18.4, J18.5, J18.6, J18.7, J18.8, U1.48 (~CS)
/~CS_SIO: J13.1, J13.2, J13.3, J13.4, J13.5, J13.6, J13.7, J13.8, U2.35 (CS)
/~DTACK: J3.62 (~BUSACK), U1.46 (~DTACK), U2.9 (DTACK)
/~IACK: R1.1, U1.45 (~IACK), U2.37 (IACK)
/~INT1: J1.1, J3.37 (USR1)
/~INT2: J1.3, J3.38 (USR2)
/~INT5: J1.5, J3.39 (USR3)
/~INT6: J1.7, J3.40 (USR4)
/~INT_MFP: J1.2, J1.4, J1.6, J1.8, U1.32 (~IRQ)
/~INT_SIO: J2.1, J2.2, J2.3, J2.4, U2.21 (IRQ)
/~LDS: J3.43 (~LDS), U1.47 (~DS)
/~RESET: J3.20 (~RESET), U1.21 (~RESET), U2.34 (RESET)
GND: C2.1, C4.1, C5.1, C9.1, C10.1, D1.1 (K), D2.1 (K), J3.17 (GND), J3.57 (GND), J5.11, J5.12, J8.15, J8.16, J15.1, J16.1, J17.1, JP7.1 (A), U1.34 (~IEI), U1.36 (GND), U2.20 (GND), U6.5 (R1), U6.9 (R3), U6.10 (GND), U6.12 (R4), U6.14 (R5), U6.16 (R6), U6.18 (R7), U7.8 (GND), X1.4 (GND)
unnamed: D1.2 (A), R2.2
unnamed: D2.2 (A), R3.2
unnamed: J4.3, X1.5 (OUT)
unnamed: J6.1, U1.13 (TAO)
unnamed: J6.3, U1.14 (TBO)
unnamed: J6.5, U1.15 (TCO)
unnamed: J6.6, U1.7 (TC), U1.10 (RC), U1.16 (TDO)
unnamed: J12.1, U7.15 (O0)
unnamed: J12.2, U7.14 (O1)
unnamed: J12.3, U7.13 (O2)
unnamed: J12.4, U7.12 (O3)
unnamed: J12.5, U7.11 (O4)
unnamed: J12.6, U7.10 (O5)
unnamed: J12.7, U7.9 (O6)
unnamed: J12.8, U7.7 (O7)
unnamed: J15.2, JP2.2 (B)
unnamed: J15.6, JP1.2 (B)
unnamed: J16.2, JP4.2 (B)
unnamed: J16.6, JP3.2 (B)
unnamed: J17.2, JP6.2 (B)
unnamed: J17.6, JP5.2 (B)
unnamed: JP7.2 (B), U2.33 (X2)
unnamed: R2.1, U2.26 (OP6)
unnamed: R3.1, U2.15 (OP7)
unnamed: U6.19 (P=R), U7.4 (E1)

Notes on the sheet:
USER LEDs
1-3 TO USE ON BOARD OSCILLATOR 1-2 TO USE EXTERNAL CLOCK 1-2 & 3-4 TO USE ON BOARD OSCILLATOR & SUPPLY CLOCK2
CS0: D00000 CS1: D00800 CS2: D01000 CS3: D01800 CS4: D02000 CS5: D02800 CS6: D03000 CS7: D03800

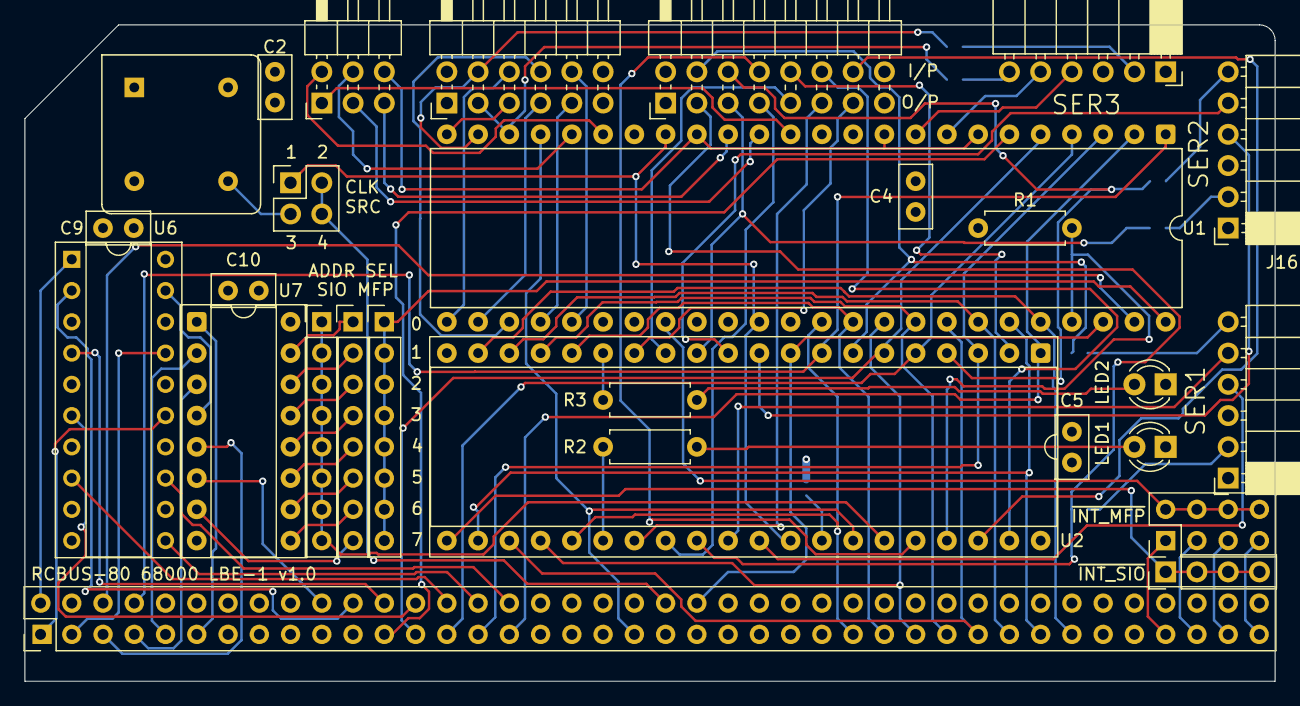
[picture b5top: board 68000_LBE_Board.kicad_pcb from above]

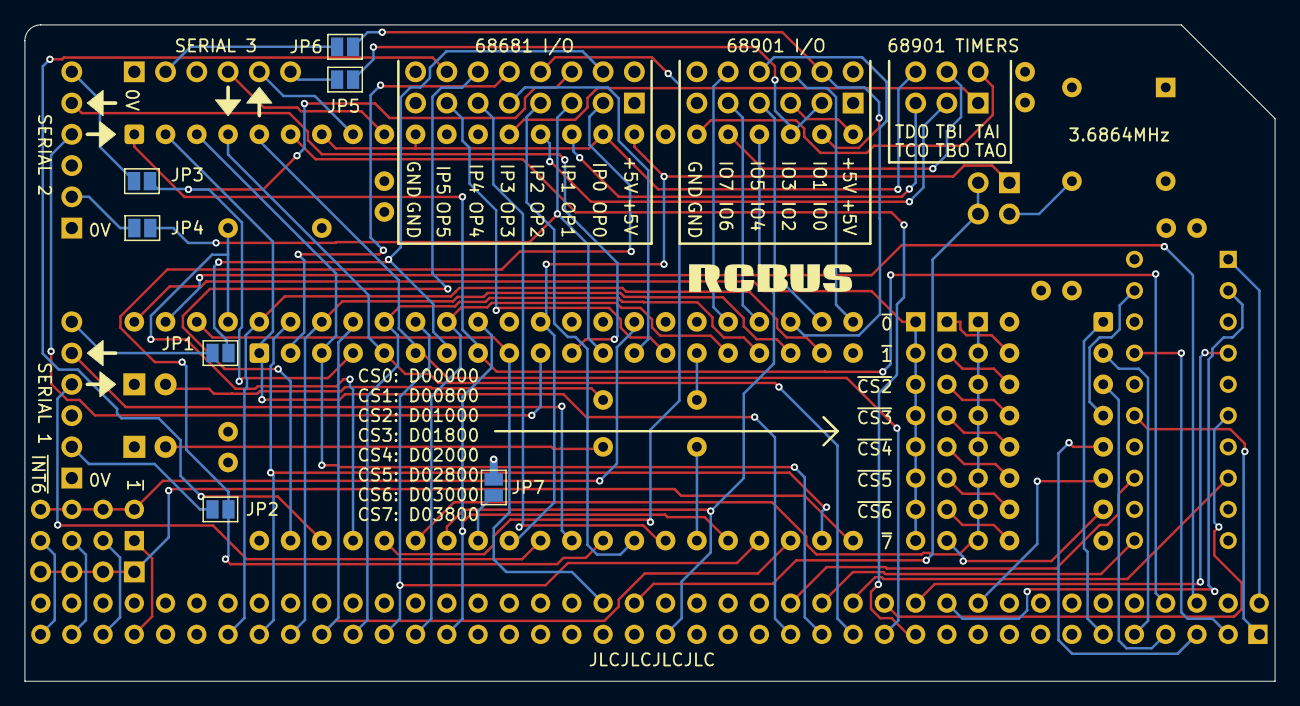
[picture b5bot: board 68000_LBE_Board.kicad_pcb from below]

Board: 4 copper layers, 101.6 x 53.3 mm, 35 parts (7 on the bottom side), 97 nets.

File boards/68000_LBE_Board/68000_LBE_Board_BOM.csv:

Reference,Value,Datasheet,Footprint,Qty,Description
"C2,C4,C5,C9,C10",100n,~,Capacitor_THT:C_Disc_D5.0mm_W2.5mm_P2.50mm,5,Unpolarized ceramic capacitor
"D1,D2",LED,~,LED_THT:LED_D3.0mm,2,Light emitting diode
J1,Conn_02x04_Odd_Even,~,MyLibrary2023:PinHeader_2x04_P2.54mm_Vertical,1,"Generic connector, double row, 02x04"
J2,Conn_01x04,~,Connector_PinHeader_2.54mm:PinHeader_1x04_P2.54mm_Vertical,1,"Generic connector, single row, 01x04, script generated (kicad-library-utils/schlib/autogen/connector/)"
J3,RCBus_80PIN_68000,~,MyLibrary2023:RCBus_80p_Medium,1,"Generic connector, double row, 02x20, right angle"
J4,Conn_02x02_Odd_Even,~,Connector_PinHeader_2.54mm:PinHeader_2x02_P2.54mm_Vertical,1,"Generic connector, double row, 02x02"
J5,Conn_02x06_Odd_Even,~,Connector_PinHeader_2.54mm:PinHeader_2x06_P2.54mm_Horizontal,1,"Generic connector, double row, 02x06, odd/even pin numbering scheme (row 1 odd numbers, row 2 even numbers), script generated (kicad-library-utils/schlib/autogen/connector/)"
J6,Conn_02x03_Odd_Even,~,Connector_PinHeader_2.54mm:PinHeader_2x03_P2.54mm_Horizontal,1,"Generic connector, double row, 02x03, odd/even pin numbering scheme (row 1 odd numbers, row 2 even numbers), script generated (kicad-library-utils/schlib/autogen/connector/)"
J8,Conn_02x08_Odd_Even,~,Connector_PinHeader_2.54mm:PinHeader_2x08_P2.54mm_Horizontal,1,"Generic connector, double row, 02x08, odd/even pin numbering scheme (row 1 odd numbers, row 2 even numbers), script generated (kicad-library-utils/schlib/autogen/connector/)"
"J12,J13,J18",Conn_01x08,~,MyLibrary2023:PinHeader_1x08_P2.54mm_Vertical,3,"Generic connector, single row, 01x08"
"J15,J16,J17",Conn_01x06,~,Connector_PinSocket_2.54mm:PinSocket_1x06_P2.54mm_Horizontal,3,"Generic connector, single row, 01x06, right angle"
"JP1,JP2,JP3,JP4,JP5,JP6",SolderJumper,~,Jumper:SolderJumper-2_P1.3mm_Open_Pad1.0x1.5mm,6,"Solder Jumper, 2-pole, open"
R1,10K,~,Resistor_THT:R_Axial_DIN0207_L6.3mm_D2.5mm_P7.62mm_Horizontal,1,
"R2,R3",1K,~,Resistor_THT:R_Axial_DIN0207_L6.3mm_D2.5mm_P7.62mm_Horizontal,2,Resistor
U1,68901P,,Package_DIP:DIP-48_W15.24mm,1,Parallel Interface
U2,68681P,,Package_DIP:DIP-40_W15.24mm_Socket,1,DUART
U6,74LS688,http://www.ti.com/lit/gpn/sn74LS688,MyLibrary2023:DIP-20_W7.62mm_Socket,1,8-bit magnitude comparator
U7,74LS138,http://www.ti.com/lit/gpn/sn74LS138,Package_DIP:DIP-16_W7.62mm_Socket,1,Decoder 3 to 8 active low outputs
X1,3.6864MHz,,Oscillator:Oscillator_DIP-8,1,"Crystal Clock Oscillator, DIP8-style metal package"
